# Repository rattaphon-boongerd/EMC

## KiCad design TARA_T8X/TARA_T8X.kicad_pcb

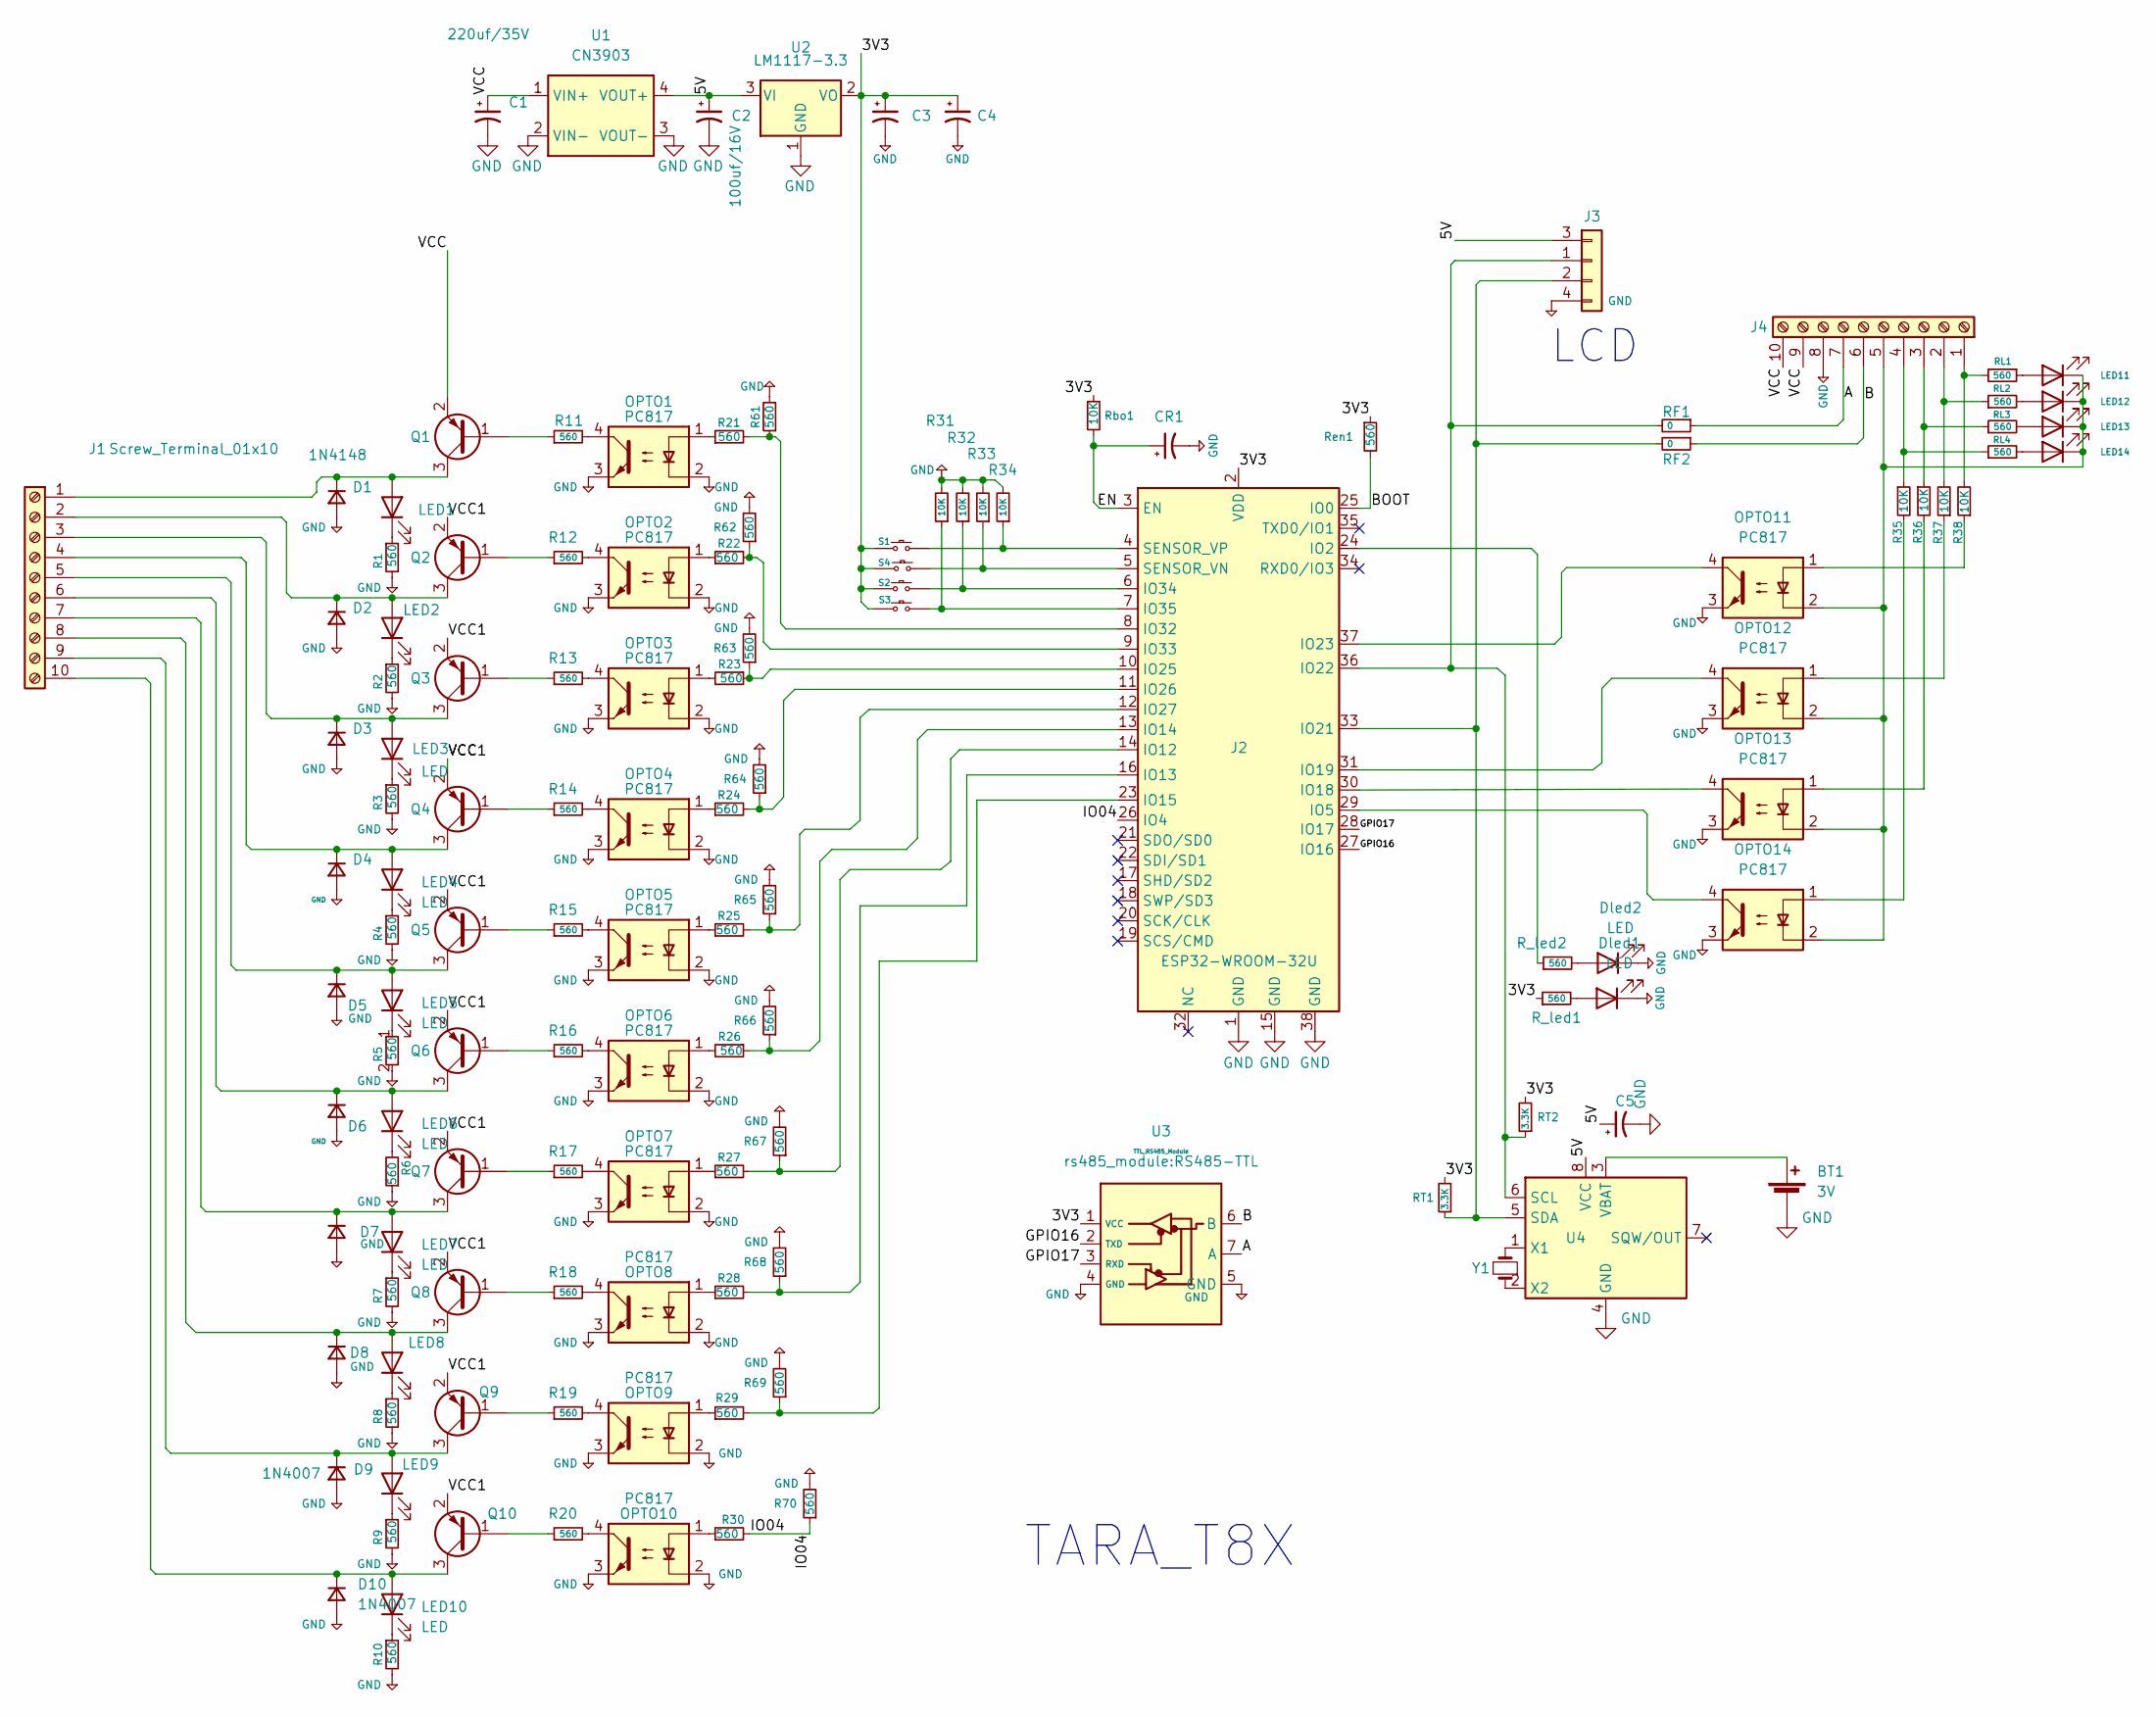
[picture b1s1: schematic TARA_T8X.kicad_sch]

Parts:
BT1: 3V; BatteryHolder_LINX_BAT-HLD-012-SMT
C1: 220uf/35V; CP_Radial_D8.0mm_P5.00mm
C2: 100uf/16V; C_0805_2012Metric
C3: 10uf/50v; C_0805_2012Metric
C4, C5: 100nF; C_0805_2012Metric
CR1: 100nF; C_0805_2012Metric
D1, D2: 1N4148; D_1206_3216Metric
D3, D4, D5, D6, D7, D8, D9, D10: 1N4007; D_1206_3216Metric
Dled1, Dled2: LED; LED_0805_2012Metric
J1, J4: Screw_Terminal_01x10; TerminalBlock_MaiXu_MX126-5.0-10P_1x10_P5.00mm
J2: ESP32-WROOM-32U; ESP32-S3-WROOM-1
J3: Conn_01x04_MountingPin; PinHeader_1x04_P2.54mm_Vertical
LED1, LED2, LED3, LED4, LED5, LED6, LED7, LED8, LED9, LED10, LED11, LED12, LED13, LED14: LED; LED_0805_2012Metric
OPTO1, OPTO2, OPTO3, OPTO4, OPTO5, OPTO6, OPTO7, OPTO8, OPTO9, OPTO10, OPTO11, OPTO12, OPTO13, OPTO14: PC817; SO-4_7.6x3.6mm_P2.54mm_1234
Q1, Q2, Q3, Q4, Q5, Q6, Q7, Q8, Q9, Q10: 2N5401; SOT-23
R1, R2, R3, R4, R5, R6, R7, R8, R9, R10, R11, R12, R13, R14, R15, R16, R17, R18, R19, R20, R21, R22, R23, R24, R25, R26, R27, R28, R29, R30, R61, R62, R63, R64, R65, R66, R67, R68, R69, R70: 560; R_0805_2012Metric
R31, R32, R33, R34, R35, R36, R37, R38: 10K; R_0805_2012Metric
RF1, RF2: 0; R_0805_2012Metric
RL1, RL2, RL3, RL4: 560; R_0805_2012Metric
RT1, RT2: 3.3K; R_0805_2012Metric
R_led1, R_led2: 560; R_0805_2012Metric
Rbo1: 10K; R_0805_2012Metric
Ren1: 560; R_0805_2012Metric
S1, S2, S3, S4: SW_Push; SW_PUSH_6mm_H5mm
U1: CN3903; DCDC5V
U2: LM1117-3.3; SOT-223-3_TabPin2
U3: TTL_RS485_Module; RS485-TTL
U4: DS1307+; SOIC-8-1EP_3.9x4.9mm_P1.27mm_EP2.29x3mm
Y1: Crystal_Small; Crystal_AT310_D3.0mm_L10.0mm_Horizontal

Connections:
/3V3: C3.1, C4.1, J2.2 (VDD), RT1.2, RT2.2, R_led1.1, Rbo1.1, Ren1.1, S1.2, S2.2, S3.2, S4.2, U2.2 (VO), U3.1 (VCC); also elsewhere on the board
/5V: C2.1, C5.1, J3.3 (Pin_1), U1.4 (VOUT+), U2.3 (VI), U4.8 (VCC); also elsewhere on the board
/A: J4.7, RF1.1, U3.7 (A)
/B: J4.6, RF2.1, U3.6 (B)
/BOOT: J2.25 (IO0), Ren1.2
/EN: CR1.1, J2.3 (EN), Rbo1.2
/GPIO16: J2.27 (IO16), U3.2 (TXD)
/GPIO17: J2.28 (IO17), U3.3 (RXD)
/IO04: J2.26 (IO4), R30.2, R70.1
/VCC: C1.1, J4.9, J4.10, Q1.2 (E), Q2.2 (E), Q3.2 (E), Q4.2 (E), Q5.2 (E), Q6.2 (E), Q7.2 (E), Q8.2 (E), Q9.2 (E), Q10.2 (E), U1.1 (VIN+)
GND: BT1.2 (-), C1.2, C2.2, C3.2, C4.2, C5.2, CR1.2, D1.2 (A), D2.2 (A), D3.2 (A), D4.2 (A), D5.2 (A), D6.2 (A), D7.2 (A), D8.2 (A), D9.2 (A), D10.2 (A), Dled1.1 (K), Dled2.1 (K), J2.1 (GND), J2.15 (GND), J2.38 (GND), J2.39 (GND), J3.4, J4.8, OPTO1.2, OPTO1.3, OPTO2.2, OPTO2.3, OPTO3.2, OPTO3.3, OPTO4.2, OPTO4.3, OPTO5.2, OPTO5.3, OPTO6.2, OPTO6.3, OPTO7.2, OPTO7.3, OPTO8.2, OPTO8.3, OPTO9.2, OPTO9.3, OPTO10.2, OPTO10.3, OPTO11.3, OPTO12.3, OPTO13.3, OPTO14.3, R1.2, R2.2, R3.2, R4.2, R5.2, R6.1, R7.2, R8.2, R9.2, R10.2, R31.2, R32.2, R33.2, R34.2, R61.2, R62.2, R63.2, R64.2, R65.2, R66.2, R67.2, R68.2, R69.2, R70.2, U1.2 (VIN-), U1.3 (VOUT-), U2.1 (GND), U3.4 (GND), U3.5 (GND), U4.4 (GND); also elsewhere on the board
unnamed: BT1.1 (+), U4.3 (VBAT)
unnamed: D1.1 (K), J1.1, LED1.2 (A), Q1.3 (C)
unnamed: D2.1 (K), J1.2, LED2.2 (A), Q2.3 (C)
unnamed: D3.1 (K), J1.3, LED3.2 (A), Q3.3 (C)
unnamed: D4.1 (K), J1.4, LED4.2 (A), Q4.3 (C)
unnamed: D5.1 (K), J1.5, LED5.2 (A), Q5.3 (C)
unnamed: D6.1 (K), J1.6, LED6.2 (A), Q6.3 (C)
unnamed: D7.1 (K), J1.7, LED7.2 (A), Q7.3 (C)
unnamed: D8.1 (K), J1.8, LED8.2 (A), Q8.3 (C)
unnamed: D9.1 (K), J1.9, LED9.2 (A), Q9.3 (C)
unnamed: D10.1 (K), J1.10, LED10.2 (A), Q10.3 (C)
unnamed: Dled1.2 (A), R_led1.2
unnamed: Dled2.2 (A), R_led2.2
unnamed: J2.24 (IO2), R_led2.1
unnamed: J2.29 (IO5), OPTO14.4
unnamed: J2.14 (IO12), R27.2, R67.1
unnamed: J2.16 (IO13), R28.2, R68.1
unnamed: J2.13 (IO14), R26.1, R66.1
unnamed: J2.23 (IO15), R29.2, R69.1
unnamed: J2.30 (IO18), OPTO13.4
unnamed: J2.31 (IO19), OPTO12.4
unnamed: J2.33 (IO21), J3.2 (Pin_3), RF2.2, RT1.1, U4.5 (SDA)
unnamed: J2.36 (IO22), J3.1 (Pin_2), RF1.2, RT2.1, U4.6 (SCL)
unnamed: J2.37 (IO23), OPTO11.4
unnamed: J2.10 (IO25), R23.1, R63.1
unnamed: J2.11 (IO26), R24.2, R64.1
unnamed: J2.12 (IO27), R25.2, R65.1
unnamed: J2.8 (IO32), R21.2, R61.1
unnamed: J2.9 (IO33), R22.2, R62.1
unnamed: J2.6 (IO34), R32.1, S2.1
unnamed: J2.7 (IO35), R31.1, S3.1
unnamed: J2.5 (SENSOR_VN), R33.1, S4.1
unnamed: J2.4 (SENSOR_VP), R34.1, S1.1
unnamed: J4.1, R38.2, RL1.2
unnamed: J4.2, R37.2, RL2.1
unnamed: J4.3, R36.1, RL3.1
unnamed: J4.4, R35.1, RL4.1
unnamed: J4.5, LED11.1 (K), LED12.1 (K), LED13.1 (K), LED14.1 (K), OPTO11.2, OPTO12.2, OPTO13.2, OPTO14.2
unnamed: LED1.1 (K), R1.1
unnamed: LED2.1 (K), R2.1
unnamed: LED3.1 (K), R3.1
unnamed: LED4.1 (K), R4.1
unnamed: LED5.1 (K), R5.1
unnamed: LED6.1 (K), R6.2
unnamed: LED7.1 (K), R7.1
unnamed: LED8.1 (K), R8.1
unnamed: LED9.1 (K), R9.1
unnamed: LED10.1 (K), R10.1
unnamed: LED11.2 (A), RL1.1
unnamed: LED12.2 (A), RL2.2
unnamed: LED13.2 (A), RL3.2
unnamed: LED14.2 (A), RL4.2
unnamed: OPTO1.1, R21.1
unnamed: OPTO1.4, R11.2
unnamed: OPTO2.1, R22.1
unnamed: OPTO2.4, R12.2
unnamed: OPTO3.1, R23.2
unnamed: OPTO3.4, R13.2
unnamed: OPTO4.1, R24.1
unnamed: OPTO4.4, R14.2
unnamed: OPTO5.1, R25.1
unnamed: OPTO5.4, R15.2
unnamed: OPTO6.1, R26.2
unnamed: OPTO6.4, R16.2
unnamed: OPTO7.1, R27.1
unnamed: OPTO7.4, R17.2
unnamed: OPTO8.1, R28.1
unnamed: OPTO8.4, R18.2
unnamed: OPTO9.1, R29.1
unnamed: OPTO9.4, R19.2
unnamed: OPTO10.1, R30.1
unnamed: OPTO10.4, R20.2
unnamed: OPTO11.1, R38.1
unnamed: OPTO12.1, R37.1
unnamed: OPTO13.1, R36.2
unnamed: OPTO14.1, R35.2
unnamed: Q1.1 (B), R11.1
unnamed: Q2.1 (B), R12.1
unnamed: Q3.1 (B), R13.1
unnamed: Q4.1 (B), R14.1
unnamed: Q5.1 (B), R15.1
unnamed: Q6.1 (B), R16.1
unnamed: Q7.1 (B), R17.1
unnamed: Q8.1 (B), R18.1
unnamed: Q9.1 (B), R19.1
unnamed: Q10.1 (B), R20.1
unnamed: U4.1 (X1), Y1.2
unnamed: U4.2 (X2), Y1.1

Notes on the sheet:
TARA_T8X
LCD

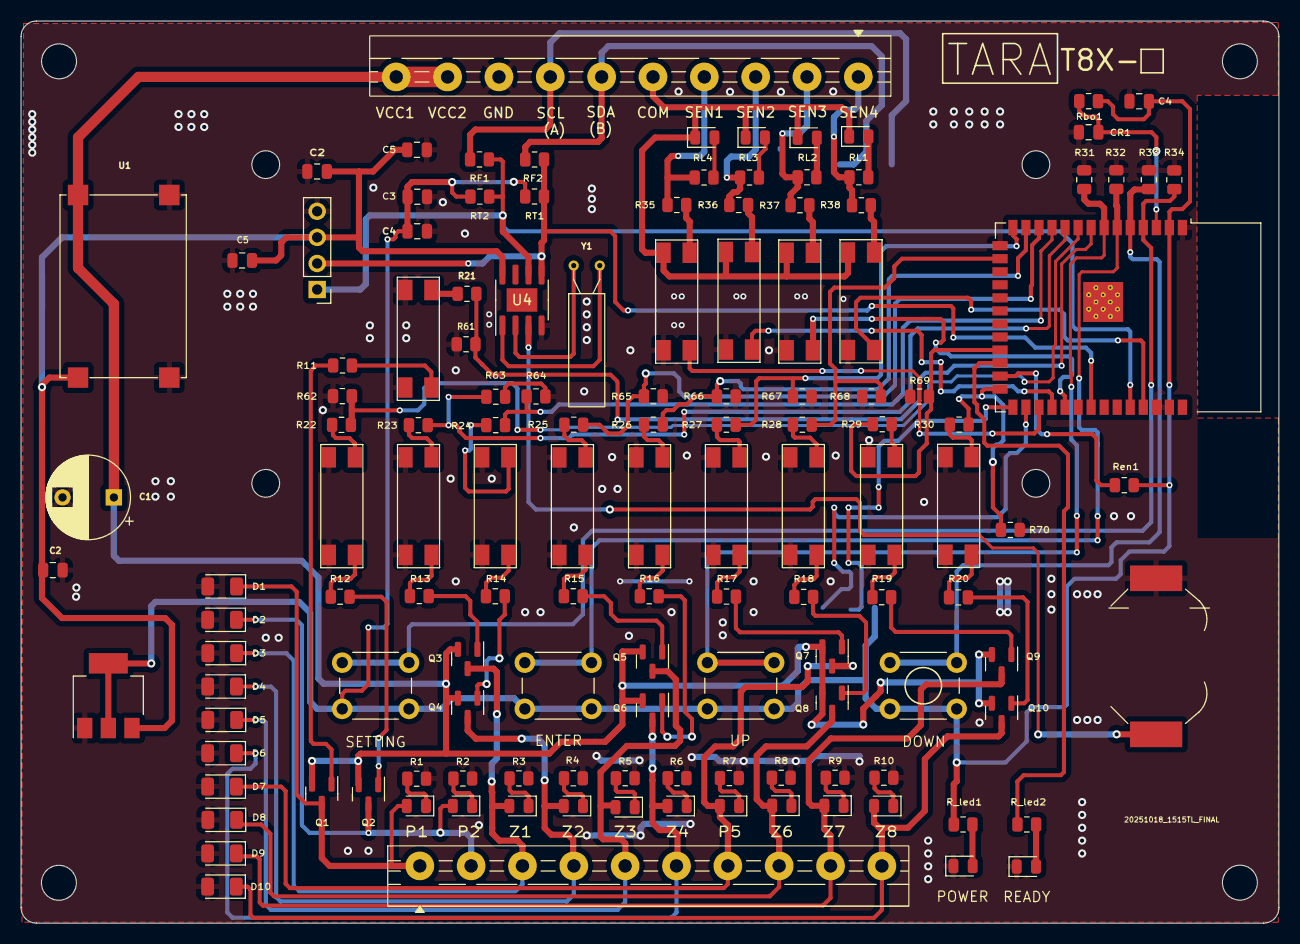
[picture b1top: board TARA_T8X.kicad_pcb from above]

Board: 2 copper layers, 122.5 x 87.9 mm, 133 parts (1 on the bottom side), 99 nets.

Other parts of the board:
C2#2: 100uf/16V; C_0805_2012Metric
C4#2, C5#2: 100nF; C_0805_2012Metric

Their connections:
/3V3: C4#2.1; also elsewhere on the board
/5V: C2#2.1, C5#2.1; also elsewhere on the board
GND: C2#2.2, C4#2.2, C5#2.2; also elsewhere on the board

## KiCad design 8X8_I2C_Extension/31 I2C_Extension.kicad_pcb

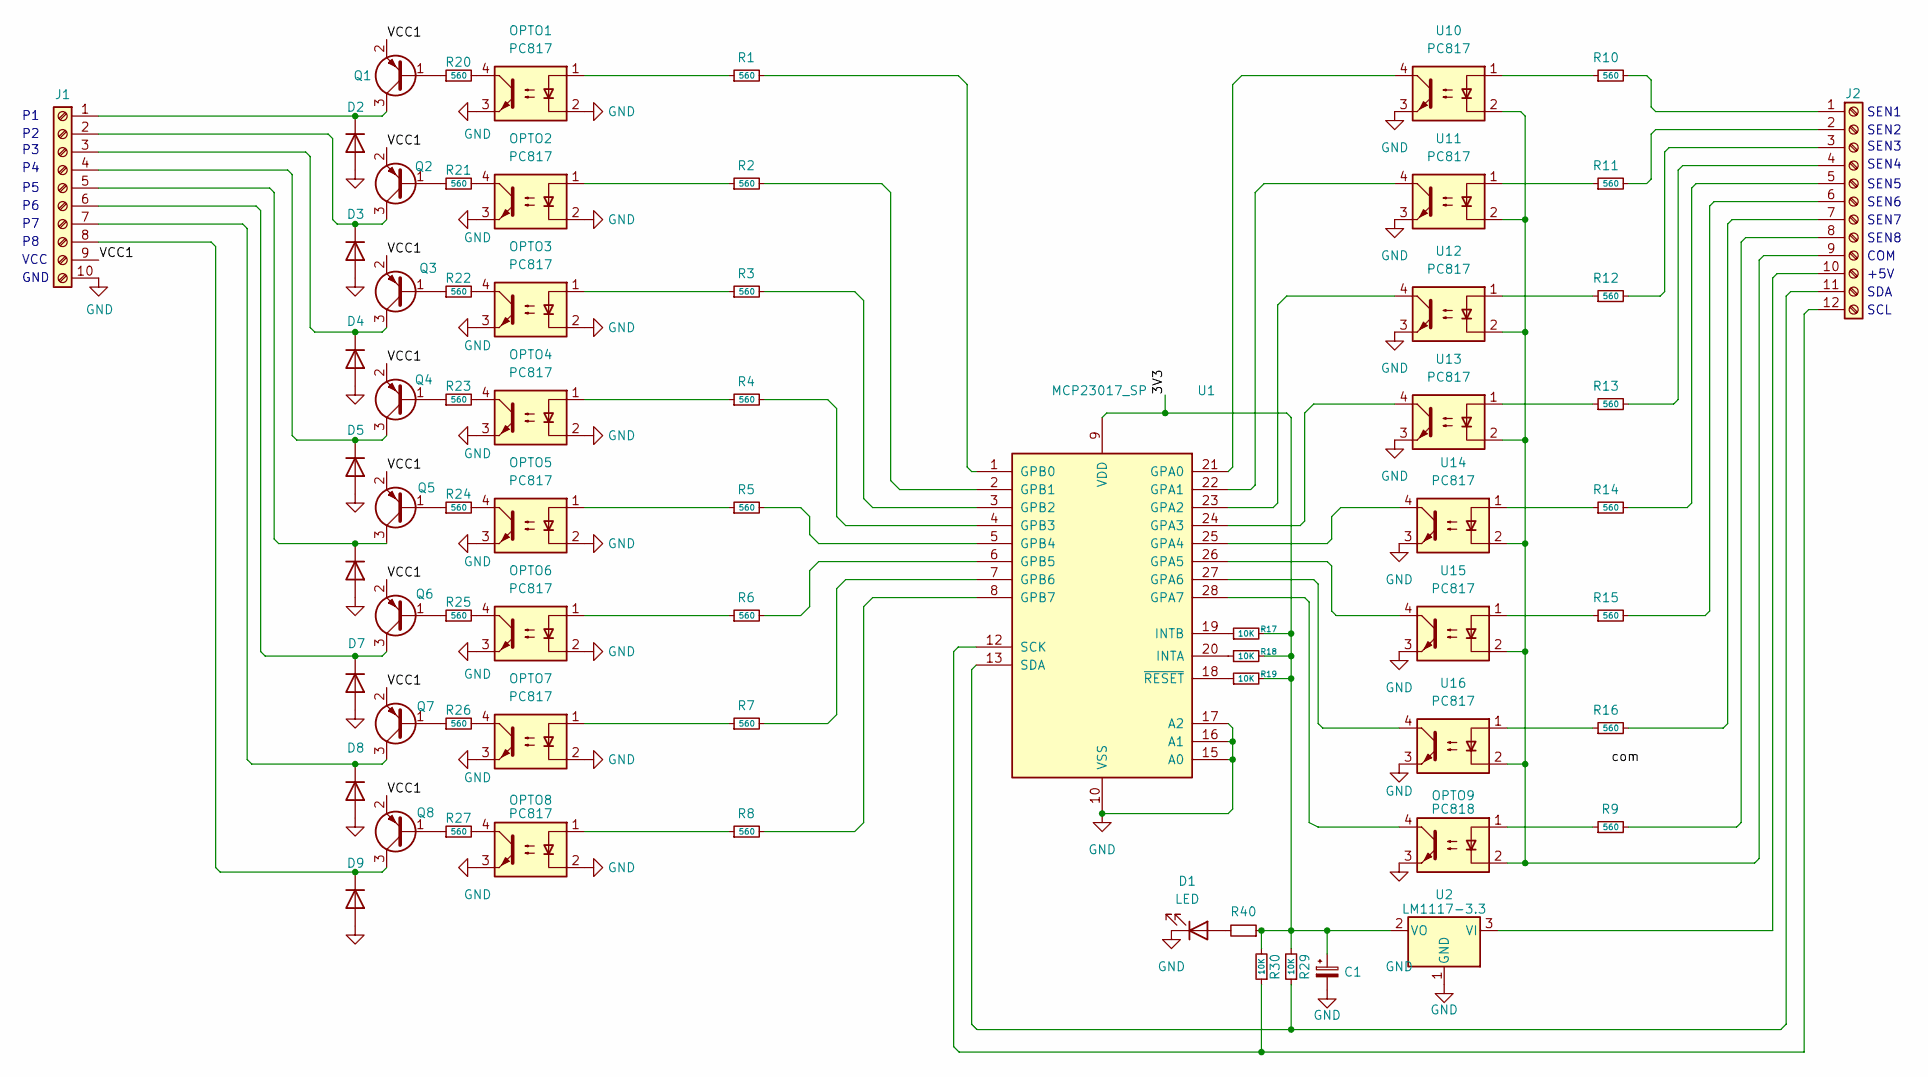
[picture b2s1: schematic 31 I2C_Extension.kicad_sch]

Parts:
C1: C_Polarized_Small; CP_Radial_D5.0mm_P2.50mm
D1: LED; LED_D5.0mm
D2, D3, D4, D5, D6, D7, D8, D9: 1N4148; D_1206_3216Metric
J1: Screw_Terminal_01x10; TerminalBlock_Phoenix_MKDS-1,5-10-5.08_1x10_P5.08mm_Horizon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
J2: Screw_Terminal_01x12; TerminalBlock_Phoenix_MKDS-1,5-12-5.08_1x12_P5.08mm_Horizon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
OPTO1, OPTO2, OPTO3, OPTO4, OPTO5, OPTO6, OPTO7, OPTO8: PC817; SO-4_7.6x3.6mm_P2.54mm_1234
OPTO9: PC818; SO-4_7.6x3.6mm_P2.54mm_1234
Q1, Q2, Q3, Q4, Q5, Q6, Q7, Q8: 2N5401; SOT-23
R1, R2, R3, R4, R5, R6, R7, R8, R9, R10, R11, R12, R13, R14, R15, R16, R20, R21, R22, R23, R24, R25, R26, R27: 560; R_0805_2012Metric
R17, R18, R19, R29, R30: 10K; R_0805_2012Metric
R40: R_Small; R_Axial_DIN0207_L6.3mm_D2.5mm_P7.62mm_Horizontal
U1: MCP23017_SP; DIP-28_W7.62mm
U2: LM1117-3.3; SOT-223-3_TabPin2
U10, U11, U12, U13, U14, U15, U16: PC817; SO-4_7.6x3.6mm_P2.54mm_1234

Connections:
/3V3: C1.1, R17.2, R18.2, R19.2, R29.2, R30.2, R40.1, U1.9 (VDD), U2.2 (VO)
/VCC1: J1.9, Q1.2 (E), Q2.2 (E), Q3.2 (E), Q4.2 (E), Q5.2 (E), Q6.2 (E), Q7.2 (E), Q8.2 (E)
GND: C1.2, D1.1 (K), D2.2 (A), D3.2 (A), D4.2 (A), D5.2 (A), D6.2 (A), D7.2 (A), D8.2 (A), D9.2 (A), J1.10, OPTO1.2, OPTO1.3, OPTO2.2, OPTO2.3, OPTO3.2, OPTO3.3, OPTO4.2, OPTO4.3, OPTO5.2, OPTO5.3, OPTO6.2, OPTO6.3, OPTO7.2, OPTO7.3, OPTO8.2, OPTO8.3, OPTO9.3, U1.10 (VSS), U1.15 (A0), U1.16 (A1), U1.17 (A2), U2.1 (GND), U10.3, U11.3, U12.3, U13.3, U14.3, U15.3, U16.3
unnamed: D1.2 (A), R40.2
unnamed: D2.1 (K), J1.1, Q1.3 (C)
unnamed: D3.1 (K), J1.2, Q2.3 (C)
unnamed: D4.1 (K), J1.3, Q3.3 (C)
unnamed: D5.1 (K), J1.4, Q4.3 (C)
unnamed: D6.1 (K), J1.5, Q5.3 (C)
unnamed: D7.1 (K), J1.6, Q6.3 (C)
unnamed: D8.1 (K), J1.7, Q7.3 (C)
unnamed: D9.1 (K), J1.8, Q8.3 (C)
unnamed: J2.1, R10.2
unnamed: J2.2, R11.2
unnamed: J2.3, R12.2
unnamed: J2.4, R13.2
unnamed: J2.5, R14.2
unnamed: J2.6, R15.2
unnamed: J2.7, R16.2
unnamed: J2.8, R9.2
unnamed: J2.9, OPTO9.2, U10.2, U11.2, U12.2, U13.2, U14.2, U15.2, U16.2
unnamed: J2.10, U2.3 (VI)
unnamed: J2.11, R29.1, U1.13 (SDA)
unnamed: J2.12, R30.1, U1.12 (SCK)
unnamed: OPTO1.1, R1.1
unnamed: OPTO1.4, R20.2
unnamed: OPTO2.1, R2.1
unnamed: OPTO2.4, R21.2
unnamed: OPTO3.1, R3.1
unnamed: OPTO3.4, R22.2
unnamed: OPTO4.1, R4.1
unnamed: OPTO4.4, R23.2
unnamed: OPTO5.1, R5.1
unnamed: OPTO5.4, R24.2
unnamed: OPTO6.1, R6.1
unnamed: OPTO6.4, R25.2
unnamed: OPTO7.1, R7.1
unnamed: OPTO7.4, R26.2
unnamed: OPTO8.1, R8.1
unnamed: OPTO8.4, R27.2
unnamed: OPTO9.1, R9.1
unnamed: OPTO9.4, U1.28 (GPA7)
unnamed: Q1.1 (B), R20.1
unnamed: Q2.1 (B), R21.1
unnamed: Q3.1 (B), R22.1
unnamed: Q4.1 (B), R23.1
unnamed: Q5.1 (B), R24.1
unnamed: Q6.1 (B), R25.1
unnamed: Q7.1 (B), R26.1
unnamed: Q8.1 (B), R27.1
unnamed: R1.2, U1.1 (GPB0)
unnamed: R2.2, U1.2 (GPB1)
unnamed: R3.2, U1.3 (GPB2)
unnamed: R4.2, U1.4 (GPB3)
unnamed: R5.2, U1.5 (GPB4)
unnamed: R6.2, U1.6 (GPB5)
unnamed: R7.2, U1.7 (GPB6)
unnamed: R8.2, U1.8 (GPB7)
unnamed: R10.1, U10.1
unnamed: R11.1, U11.1
unnamed: R12.1, U12.1
unnamed: R13.1, U13.1
unnamed: R14.1, U14.1
unnamed: R15.1, U15.1
unnamed: R16.1, U16.1
unnamed: R17.1, U1.19 (INTB)
unnamed: R18.1, U1.20 (INTA)
unnamed: R19.1, U1.18 (~RESET)
unnamed: U1.21 (GPA0), U10.4
unnamed: U1.22 (GPA1), U11.4
unnamed: U1.23 (GPA2), U12.4
unnamed: U1.24 (GPA3), U13.4
unnamed: U1.25 (GPA4), U14.4
unnamed: U1.26 (GPA5), U15.4
unnamed: U1.27 (GPA6), U16.4

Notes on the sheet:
VCC
SEN5
SDA
SEN3
COM
+5V
GND
SEN6
SEN4
SCL
SEN8
SEN1
SEN7
SEN2

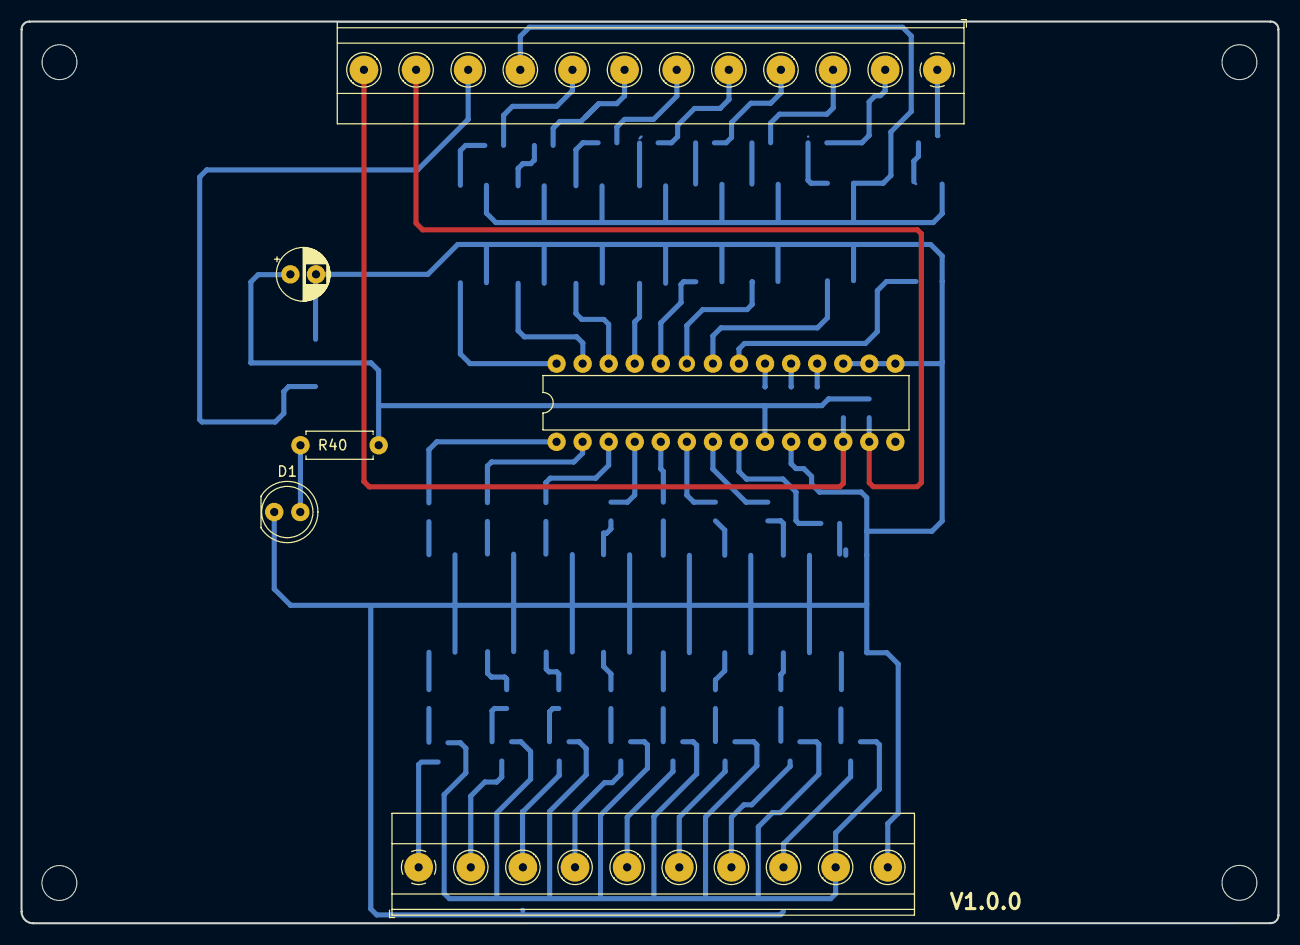
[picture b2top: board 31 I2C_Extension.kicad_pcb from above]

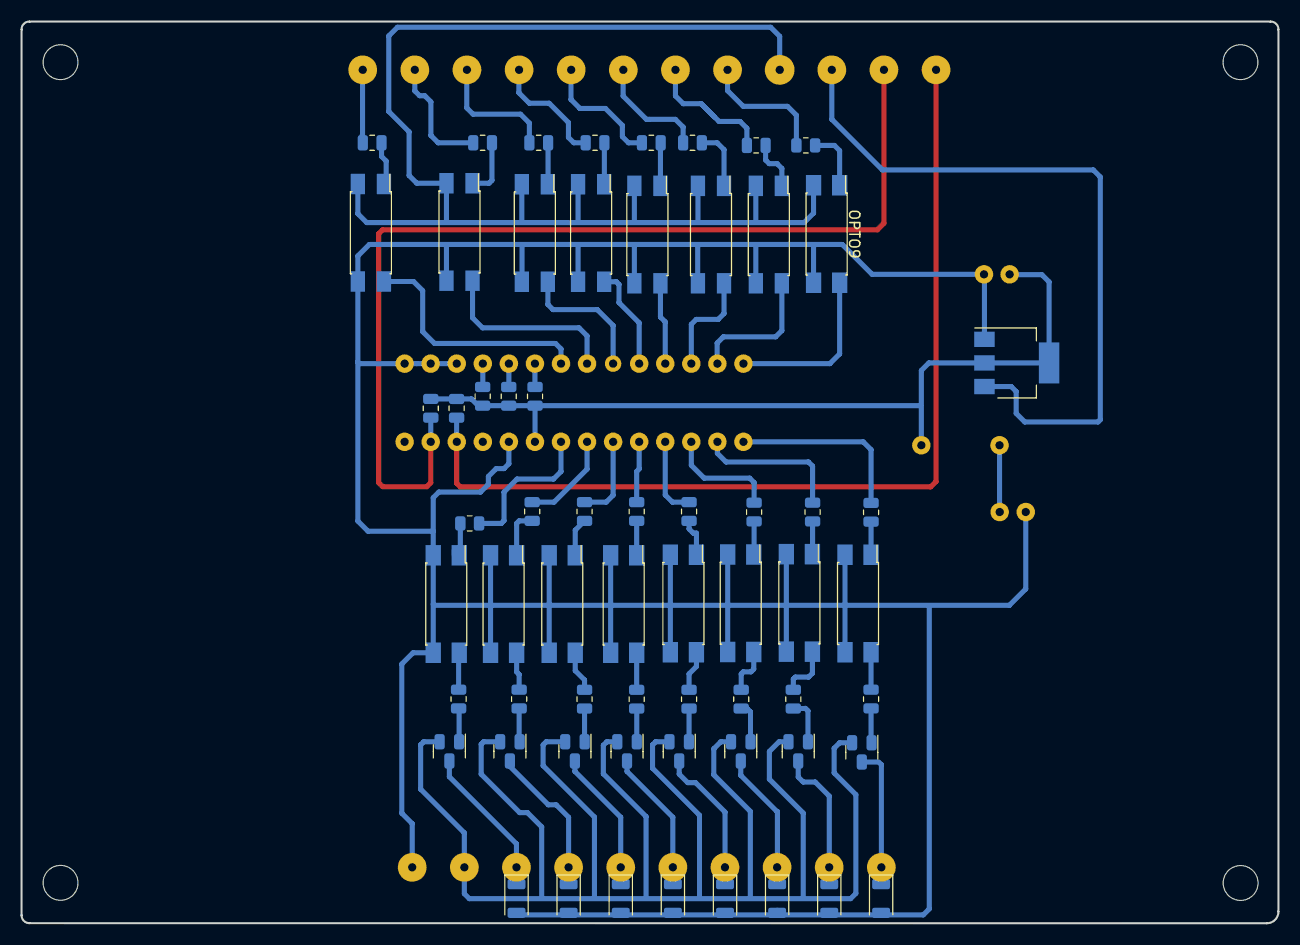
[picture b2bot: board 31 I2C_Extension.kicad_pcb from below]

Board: 2 copper layers, 122.5 x 87.9 mm, 68 parts (62 on the bottom side), 75 nets.

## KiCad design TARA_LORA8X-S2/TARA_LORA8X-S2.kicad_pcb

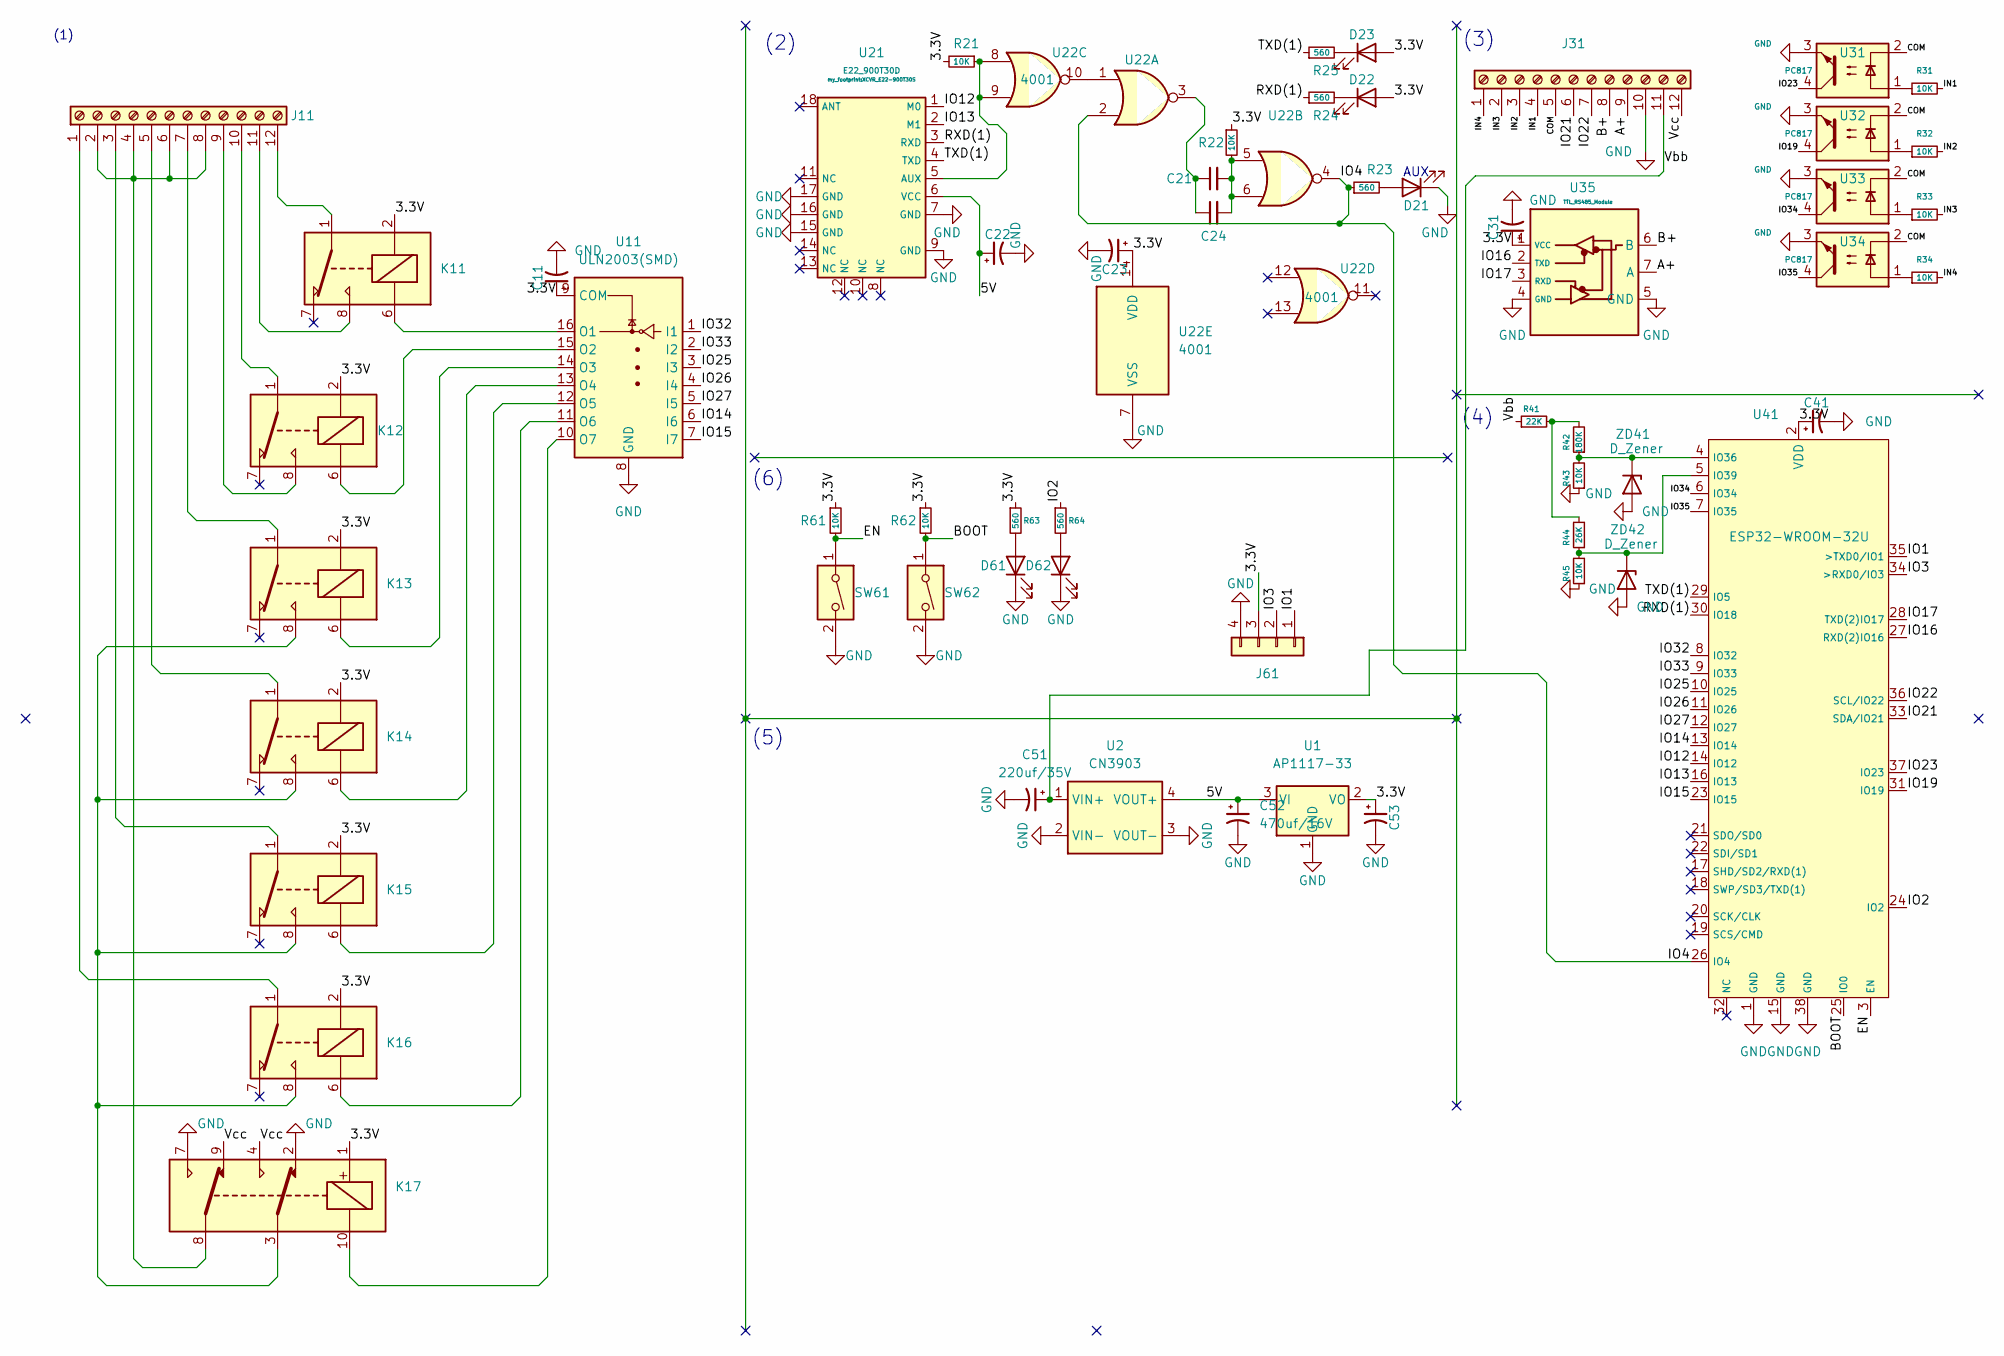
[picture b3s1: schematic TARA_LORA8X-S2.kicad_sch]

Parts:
C11, C22, C23, C31, C41: 100nF; C_0805_2012Metric
C21: 47uf/50V; CP_Radial_D6.3mm_P2.50mm
C24, C53: 47uf/50V; C_0805_2012Metric
C51: 220uf/35V; CP_Radial_D8.0mm_P5.00mm
C52: 470uf/16V; CP_Radial_D6.3mm_P2.50mm
D21, D22, D23, D61, D62: LED; LED_0805_2012Metric
J11, J31: Screw_Terminal_01x12; TerminalBlock_Phoenix_MKDS-1,5-12-5.08_1x12_P5.08mm_Horizon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
J61: Conn_01x04; PinHeader_1x04_P2.54mm_Horizontal
K11, K12, K13, K14, K15, K16: HRS1H-S-DC3V
K17: HRS2H-S-DC3V
R21, R22, R31, R32, R33, R34, R43, R45, R61, R62: 10K; R_0805_2012Metric
R23, R24, R25, R63, R64: 560; R_0805_2012Metric
R41: 22K; R_0805_2012Metric
R42: 180K; R_0805_2012Metric
R44: 26K; R_0805_2012Metric
SW61, SW62: SW_DIP_x01; SW_PUSH_6mm_H4.3mm
U1: AP1117-33; SOT-223-3_TabPin2
U2: CN3903; DCDC5V
U11: ULN2003(SMD); SO-16_3.9x9.9mm_P1.27mm
U21: E22_900T30D; XCVR_E22-900T30S
U22: 4001; SO-14_3.9x8.65mm_P1.27mm
U31, U32, U33, U34: PC817; DIP-4_W7.62mm
U35: TTL_RS485_Module; RS485-TTL
U41: ESP32-WROOM-32U
ZD41, ZD42: D_Zener; D_SOD-123

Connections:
/3.3V: C11.1, C23.1, C31.1, C41.1, C53.1, D22.2 (A), D23.2 (A), J61.3, K11.2, K12.2, K13.2, K14.2, K15.2, K16.2, K17.1, R21.2, R22.1, R61.1, R62.1, R63.1, U1.2 (VO), U11.9 (COM), U22.14 (VDD), U35.1 (VCC), U41.2 (VDD)
/5V: C22.1, C52.1, U1.3 (VI), U2.4 (VOUT+), U21.6 (VCC)
/A+: J31.9, U35.7 (A)
/B+: J31.8, U35.6 (B)
/BOOT: R62.2, SW62.1, U41.25 (IO0)
/COM: J31.5, U31.2, U32.2, U33.2, U34.2
/EN: R61.2, SW61.1, U41.3 (EN)
/IN1: J31.4, R31.2
/IN2: J31.3, R32.2
/IN3: J31.2, R33.2
/IN4: J31.1, R34.2
/IO1: J61.1, U41.35 (>TXD0/IO1)
/IO2: R64.1, U41.24 (IO2)
/IO3: J61.2, U41.34 (>RXD0/IO3)
/IO4: R23.1, U22.2, U22.4, U41.26 (IO4)
/IO12: U21.1 (M0), U41.14 (IO12)
/IO13: U21.2 (M1), U41.16 (IO13)
/IO14: U11.6 (I6), U41.13 (IO14)
/IO15: U11.7 (I7), U41.23 (IO15)
/IO16: U35.2 (TXD), U41.27 (RXD(2)IO16)
/IO17: U35.3 (RXD), U41.28 (TXD(2)IO17)
/IO19: U32.4, U41.31 (IO19)
/IO21: J31.6, U41.33 (SDA/IO21)
/IO22: J31.7, U41.36 (SCL/IO22)
/IO23: U31.4, U41.37 (IO23)
/IO25: U11.3 (I3), U41.10 (IO25)
/IO26: U11.4 (I4), U41.11 (IO26)
/IO27: U11.5 (I5), U41.12 (IO27)
/IO32: U11.1 (I1), U41.8 (IO32)
/IO33: U11.2 (I2), U41.9 (IO33)
/IO34: U33.4, U41.6 (IO34)
/IO35: U34.4, U41.7 (IO35)
/RXD(1): R24.1, U21.3 (RXD), U41.30 (IO18)
/TXD(1): R25.1, U21.4 (TXD), U41.29 (IO5)
/Vbb: C51.1, J31.11, R41.1, U2.1 (VIN+)
/Vcc: J31.12, K17.4, K17.9
GND: C11.2, C22.2, C23.2, C31.2, C41.2, C51.2, C52.2, C53.2, D21.1 (K), D61.1 (K), D62.1 (K), J31.10, J61.4, K17.2, K17.7, R43.1, R45.1, SW61.2, SW62.2, U1.1 (GND), U2.2 (VIN-), U2.3 (VOUT-), U11.8 (GND), U21.7 (GND), U21.9 (GND), U21.15 (GND), U21.16 (GND), U21.17 (GND), U22.7 (VSS), U31.3, U32.3, U33.3, U34.3, U35.4 (GND), U35.5 (GND), U41.1 (GND), U41.15 (GND), U41.38 (GND), ZD41.2 (A), ZD42.2 (A)
unnamed: C21.1, C24.1, U22.3
unnamed: C21.2, C24.2, R22.2, U22.5, U22.6
unnamed: D21.2 (A), R23.2
unnamed: D22.1 (K), R24.2
unnamed: D23.1 (K), R25.2
unnamed: D61.2 (A), R63.2
unnamed: D62.2 (A), R64.2
unnamed: J11.1, K16.1
unnamed: J11.2, J11.4, J11.6, J11.8, K17.8
unnamed: J11.3, K15.1
unnamed: J11.5, K14.1
unnamed: J11.7, K13.1
unnamed: J11.9, K12.8
unnamed: J11.10, K12.1
unnamed: J11.11, K11.8
unnamed: J11.12, K11.1
unnamed: K11.6, U11.16 (O1)
unnamed: K12.6, U11.15 (O2)
unnamed: K13.6, U11.14 (O3)
unnamed: K13.8, K14.8, K15.8, K16.8, K17.3
unnamed: K14.6, U11.13 (O4)
unnamed: K15.6, U11.12 (O5)
unnamed: K16.6, U11.11 (O6)
unnamed: K17.10, U11.10 (O7)
unnamed: R21.1, U21.5 (AUX), U22.8, U22.9
unnamed: R31.1, U31.1
unnamed: R32.1, U32.1
unnamed: R33.1, U33.1
unnamed: R34.1, U34.1
unnamed: R41.2, R42.2, R44.2
unnamed: R42.1, R43.2, U41.4 (IO36), ZD41.1 (K)
unnamed: R44.1, R45.2, U41.5 (IO39), ZD42.1 (K)
unnamed: U22.1, U22.10

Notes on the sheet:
(3)
AUX
(6)
(1)
(2)
(4)
(5)

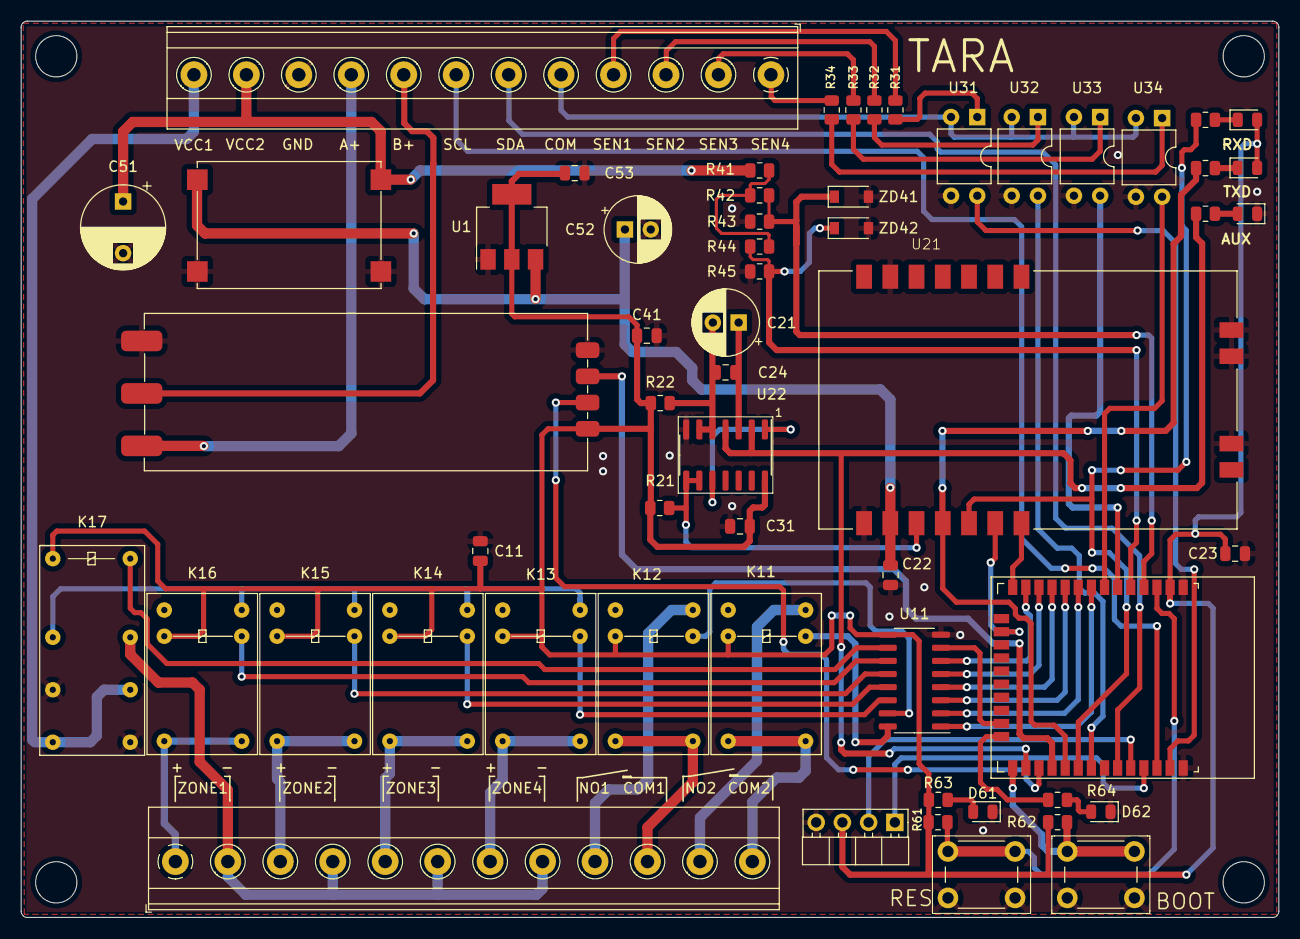
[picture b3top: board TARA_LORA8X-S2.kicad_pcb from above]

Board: 2 copper layers, 121.8 x 86.8 mm, 58 parts (0 on the bottom side), 70 nets.

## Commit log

2025-04-14 tata_timer t8x ล่าสุดย้ายมาจาก EMC Local Machine
2025-04-14 เพื่มวงจรมาจากเดิม
2025-04-14 ยกเลิก R-Pullup 47K
2025-04-14 PCB-V2.8.3
2025-04-14 gerber PCB-V2.8.3
2025-04-14 add TARA_LORA8X-S2
2025-04-18 เพิ่ม 8X8_I2C_Extension
2025-04-18 add versions screen on pcb 8x8 i2c
2025-04-18 edit hold size S4, RL1-4 screen--> 0.8mm
2025-04-19 add I/O identifi
2025-05-11 edit new_version T8X 12-05-25
2025-10-04 ล่าสุดวันเสาร์ที่4ตุลาคม68
    rer
2025-10-04 202510041905
2025-10-04 202504101905
    GreenSave windowsๅ11 kicad9.0
2025-10-05 202506100619_home_win10_kicad9
2025-10-05 202510060643
2025-10-06 20251006_grennsave_win10_kicad9
2025-10-06 202510061930_greensave
2025-10-06 202510061940_greensave
2025-10-07 202510071819_greensave
2025-10-08 greensave202510081256
2025-10-08 202510081700_greensave
2025-10-09 202510100658_Analab
2025-10-10 202510100958_greensave_allConnectFinish
2025-10-10 202510101205_greensave_creatGERBER
2025-10-10 202510100506_greensave
2025-10-11 202510110303_TARA_win10_kicad9
2025-10-11 202510110414_tara_win10_kicad9
2025-10-13 202510131212
2025-10-13 202510131718_TARA_linux
2025-10-16 202510161151_Greensave_linux
2025-10-16 202510161400_greensave_win10
2025-10-16 [200~20251016_G1730L
2025-10-16 20251016_G1730L
2025-10-16 20251017_A0615W
2025-10-17 20251016_G1700L
2025-10-18 20251018_1500TL
2025-10-18 20251018_1515TL_FINAL
2025-10-22 20251022_T1538L
